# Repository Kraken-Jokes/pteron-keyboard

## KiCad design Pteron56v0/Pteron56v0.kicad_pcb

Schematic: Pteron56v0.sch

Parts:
C1, C4: 22p; 22pf_0603
C2, C3, C5: .1u; .1uf_0805
C6: 1u; .1uf_0805
C7: 10u; .1uf_0805
D1, D2, D3, D4, D5, D6, D7, D8, D9, D10, D11, D12, D13, D14, D15, D16, D17, D18, D19, D20, D21, D22, D23, D24, D25, D26, D27, D28, D29, D30, D31, D32, D33, D34, D35, D36, D37, D38, D39, D40, D41, D42, D43, D44, D45, D46, D47, D48, D49, D50, D51, D52, D53, D54, D55, D56: 1N4148; D_DO-35_SOD27_P7.62mm_Horizontal
D57, D58, D59, D60, D61, D62, D63, D64, D65, D66, D67, D68, D69, D70, D71, D72, D73, D74, D75, D76, D77, D78, D79, D80, D81, D82, D83, D84, D85, D86, D87, D88, D89, D90, D91, D92, D93, D94, D95, D96, D97, D98, D99, D100, D101, D102, D103, D104, D105, D106, D107, D108, D109, D110, D111, D112: LED; LED_0402_1005Metric
F1: 500mA; Fuse_0402_1005Metric
J1: USB_C_Receptacle_USB2.0; USB_C_Receptacle_XKB_U262-16XN-4BVC11
Q1: 2N2219; TO-39-3
R1, R2: 5.1k; R_0603_1608Metric
R3, R6: 10k; 10K_Resistor
R4, R5: 22; R_0805
R7: 10k; R_0805_2012Metric
R8, R9, R10, R11, R12, R13, R14, R15, R16, R17, R18, R19, R20, R21, R22, R23, R24, R25, R26, R27, R28, R29, R30, R31, R32, R33, R34, R35, R36, R37, R38, R39, R40, R41, R42, R43, R44, R45, R46, R47, R48, R49, R50, R51, R52, R53, R54, R55, R56, R57, R58, R59, R60, R61, R62, R63: 1k; R_0805_2012Metric
SW1, SW2, SW3, SW4, SW5, SW6, SW7, SW8, SW9, SW10, SW11, SW12, SW13, SW14, SW15, SW16, SW17, SW18, SW19, SW20, SW21, SW22, SW23, SW24, SW25, SW26, SW27, SW28, SW29, SW30, SW31, SW32, SW33, SW34, SW35, SW36, SW37, SW38, SW39, SW40, SW41, SW42, SW43, SW44, SW45, SW46, SW47, SW48, SW49, SW50, SW51, SW52, SW53, SW54, SW55, SW56: SW_PUSH; Mx_Alps_100
SW57: SW_PUSH; SW_SPST_TL3342
U1: USBLC6-2SC6; SOT-23-6
U2: ATmega32U4-AU; TQFP-44_10x10mm_P0.8mm
X1: XTAL_GND; crystal_FA238-TSX3225

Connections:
Col0: D1.1 (K), D2.1 (K), D3.1 (K), D4.1 (K), D5.1 (K), U2.32
Col1: D6.1 (K), D7.1 (K), D8.1 (K), D9.1 (K), D10.1 (K), U2.31
Col2: D11.1 (K), D12.1 (K), D13.1 (K), D14.1 (K), D15.1 (K), U2.38
Col3: D16.1 (K), D17.1 (K), D18.1 (K), D19.1 (K), D20.1 (K), U2.39
Col4: D21.1 (K), D22.1 (K), D23.1 (K), D24.1 (K), U2.40
Col5: D25.1 (K), D26.1 (K), D27.1 (K), D28.1 (K), U2.41
Col6: D29.1 (K), D30.1 (K), D31.1 (K), D32.1 (K), U2.11
Col7: D33.1 (K), D34.1 (K), D35.1 (K), D36.1 (K), U2.25
Col8: D37.1 (K), D38.1 (K), D39.1 (K), D40.1 (K), D41.1 (K), U2.26
Col9: D42.1 (K), D43.1 (K), D44.1 (K), D45.1 (K), D46.1 (K), U2.27
Col10: D47.1 (K), D48.1 (K), D49.1 (K), D50.1 (K), D51.1 (K), U2.30
Col11: D52.1 (K), D53.1 (K), D54.1 (K), D55.1 (K), D56.1 (K), U2.28
unnamed: C1.1, U2.17, X1.1
unnamed: C4.1, U2.16, X1.2
unnamed: C6.1, U2.6
unnamed: D1.2 (A), SW1.2
unnamed: D2.2 (A), SW2.2
unnamed: D3.2 (A), SW3.2
unnamed: D4.2 (A), SW4.2
unnamed: D5.2 (A), SW5.2
unnamed: D6.2 (A), SW6.2
unnamed: D7.2 (A), SW7.2
unnamed: D8.2 (A), SW8.2
unnamed: D9.2 (A), SW9.2
unnamed: D10.2 (A), SW10.2
unnamed: D11.2 (A), SW11.2
unnamed: D12.2 (A), SW12.2
unnamed: D13.2 (A), SW13.2
unnamed: D14.2 (A), SW14.2
unnamed: D15.2 (A), SW15.2
unnamed: D16.2 (A), SW16.2
unnamed: D17.2 (A), SW17.2
unnamed: D18.2 (A), SW18.2
unnamed: D19.2 (A), SW19.2
unnamed: D20.2 (A), SW20.2
unnamed: D21.2 (A), SW21.2
unnamed: D22.2 (A), SW22.2
unnamed: D23.2 (A), SW23.2
unnamed: D24.2 (A), SW24.2
unnamed: D25.2 (A), SW25.2
unnamed: D26.2 (A), SW26.2
unnamed: D27.2 (A), SW27.2
unnamed: D28.2 (A), SW28.2
unnamed: D29.2 (A), SW29.2
unnamed: D30.2 (A), SW30.2
unnamed: D31.2 (A), SW31.2
unnamed: D32.2 (A), SW32.2
unnamed: D33.2 (A), SW33.2
unnamed: D34.2 (A), SW34.2
unnamed: D35.2 (A), SW35.2
unnamed: D36.2 (A), SW36.2
unnamed: D37.2 (A), SW37.2
unnamed: D38.2 (A), SW38.2
unnamed: D39.2 (A), SW39.2
unnamed: D40.2 (A), SW40.2
unnamed: D41.2 (A), SW41.2
unnamed: D42.2 (A), SW42.2
unnamed: D43.2 (A), SW43.2
unnamed: D44.2 (A), SW44.2
unnamed: D45.2 (A), SW45.2
unnamed: D46.2 (A), SW46.2
unnamed: D47.2 (A), SW47.2
unnamed: D48.2 (A), SW48.2
unnamed: D49.2 (A), SW49.2
unnamed: D50.2 (A), SW50.2
unnamed: D51.2 (A), SW51.2
unnamed: D52.2 (A), SW52.2
unnamed: D53.2 (A), SW53.2
unnamed: D54.2 (A), SW54.2
unnamed: D55.2 (A), SW55.2
unnamed: D56.2 (A), SW56.2
unnamed: D57.2 (A), R8.1
unnamed: D58.2 (A), R9.1
unnamed: D59.2 (A), R10.1
unnamed: D60.2 (A), R11.1
unnamed: D61.2 (A), R12.1
unnamed: D62.2 (A), R13.1
unnamed: D63.2 (A), R14.1
unnamed: D64.2 (A), R15.1
unnamed: D65.2 (A), R16.1
unnamed: D66.2 (A), R17.1
unnamed: D67.2 (A), R18.1
unnamed: D68.2 (A), R19.1
unnamed: D69.2 (A), R20.1
unnamed: D70.2 (A), R21.1
unnamed: D71.2 (A), R22.1
unnamed: D72.2 (A), R23.1
unnamed: D73.2 (A), R24.1
unnamed: D74.2 (A), R25.1
unnamed: D75.2 (A), R26.1
unnamed: D76.2 (A), R27.1
unnamed: D77.2 (A), R28.1
unnamed: D78.2 (A), R29.1
unnamed: D79.2 (A), R30.1
unnamed: D80.2 (A), R31.1
unnamed: D81.2 (A), R32.1
unnamed: D82.2 (A), R33.1
unnamed: D83.2 (A), R34.1
unnamed: D84.2 (A), R35.1
unnamed: D85.2 (A), R36.1
unnamed: D86.2 (A), R37.1
unnamed: D87.2 (A), R38.1
unnamed: D88.2 (A), R39.1
unnamed: D89.2 (A), R40.1
unnamed: D90.2 (A), R41.1
unnamed: D91.2 (A), R42.1
unnamed: D92.2 (A), R43.1
unnamed: D93.2 (A), R44.1
unnamed: D94.2 (A), R45.1
unnamed: D95.2 (A), R46.1
unnamed: D96.2 (A), R47.1
unnamed: D98.2 (A), R49.1
unnamed: D99.2 (A), R50.1
unnamed: D57.1 (K), D58.1 (K), D59.1 (K), D60.1 (K), D61.1 (K), D62.1 (K), D63.1 (K), D64.1 (K), D65.1 (K), D66.1 (K), D67.1 (K), D68.1 (K), D69.1 (K), D70.1 (K), D71.1 (K), D72.1 (K), D73.1 (K), D74.1 (K), D75.1 (K), D76.1 (K), D77.1 (K), D78.1 (K), D79.1 (K), D80.1 (K), D81.1 (K), D82.1 (K), D83.1 (K), D84.1 (K), D85.1 (K), D86.1 (K), D87.1 (K), D88.1 (K), D89.1 (K), D90.1 (K), D91.1 (K), D92.1 (K), D93.1 (K), D94.1 (K), D95.1 (K), D96.1 (K), D97.1 (K), D98.1 (K), D99.1 (K), D100.1 (K), D101.1 (K), D102.1 (K), D103.1 (K), D104.1 (K), D105.1 (K), D106.1 (K), D107.1 (K), D108.1 (K), D109.1 (K), D110.1 (K), D111.1 (K), D112.1 (K), Q1.1 (E)
unnamed: D100.2 (A), R51.1
unnamed: D101.2 (A), R52.1
unnamed: D102.2 (A), R53.1
unnamed: D103.2 (A), R54.1
unnamed: D104.2 (A), R55.1
unnamed: D105.2 (A), R56.1
unnamed: D106.2 (A), R57.1
unnamed: D107.2 (A), R58.1
unnamed: D108.2 (A), R59.1
unnamed: D109.2 (A), R60.1
unnamed: D110.2 (A), R61.1
unnamed: D111.2 (A), R62.1
unnamed: D112.2 (A), R63.1
unnamed: F1.2, J1.A4, J1.A9, J1.B4, J1.B9
unnamed: J1.A5, R1.2
unnamed: J1.A6, J1.B6, U1.6
unnamed: J1.A7, J1.B7, U1.4
unnamed: J1.B5, R2.2
unnamed: Q1.2 (B), R7.1, U2.29
unnamed: R3.1, SW57.2, U2.13
unnamed: R4.1, U2.4
unnamed: R4.2, U1.1
unnamed: R5.1, U2.3
unnamed: R5.2, U1.3
unnamed: R6.2, U2.33
Row0: SW1.1, SW6.1, SW11.1, SW16.1, SW21.1, SW25.1, SW29.1, SW33.1, SW37.1, SW42.1, SW47.1, SW52.1, U2.10
Row1: SW2.1, SW7.1, SW12.1, SW17.1, SW22.1, SW26.1, SW30.1, SW34.1, SW38.1, SW43.1, SW48.1, SW53.1, U2.9
Row2: SW3.1, SW8.1, SW13.1, SW18.1, SW23.1, SW27.1, SW31.1, SW35.1, SW39.1, SW44.1, SW49.1, SW54.1, U2.20
Row3: SW4.1, SW9.1, SW14.1, SW19.1, SW24.1, SW28.1, SW32.1, SW36.1, SW40.1, SW45.1, SW50.1, SW55.1, U2.21
Row4: SW5.1, SW10.1, SW15.1, SW20.1, SW41.1, SW46.1, SW51.1, SW56.1, U2.37
VCC: R8.2, R9.2, R10.2, R11.2, R12.2, R13.2, R14.2, R15.2, R16.2, R17.2, R18.2, R19.2, R20.2, R21.2, R22.2, R23.2, R24.2, R25.2, R26.2, R27.2, R28.2, R29.2, R30.2, R31.2, R32.2, R33.2, R34.2, R35.2, R36.2, R37.2, R38.2, R39.2, R40.2, R41.2, R42.2, R43.2, R44.2, R45.2, R46.2, R47.2, R48.2, R49.2, R50.2, R51.2, R52.2, R53.2, R54.2, R55.2, R56.2, R57.2, R58.2, R59.2, R60.2, R61.2, R62.2, R63.2

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
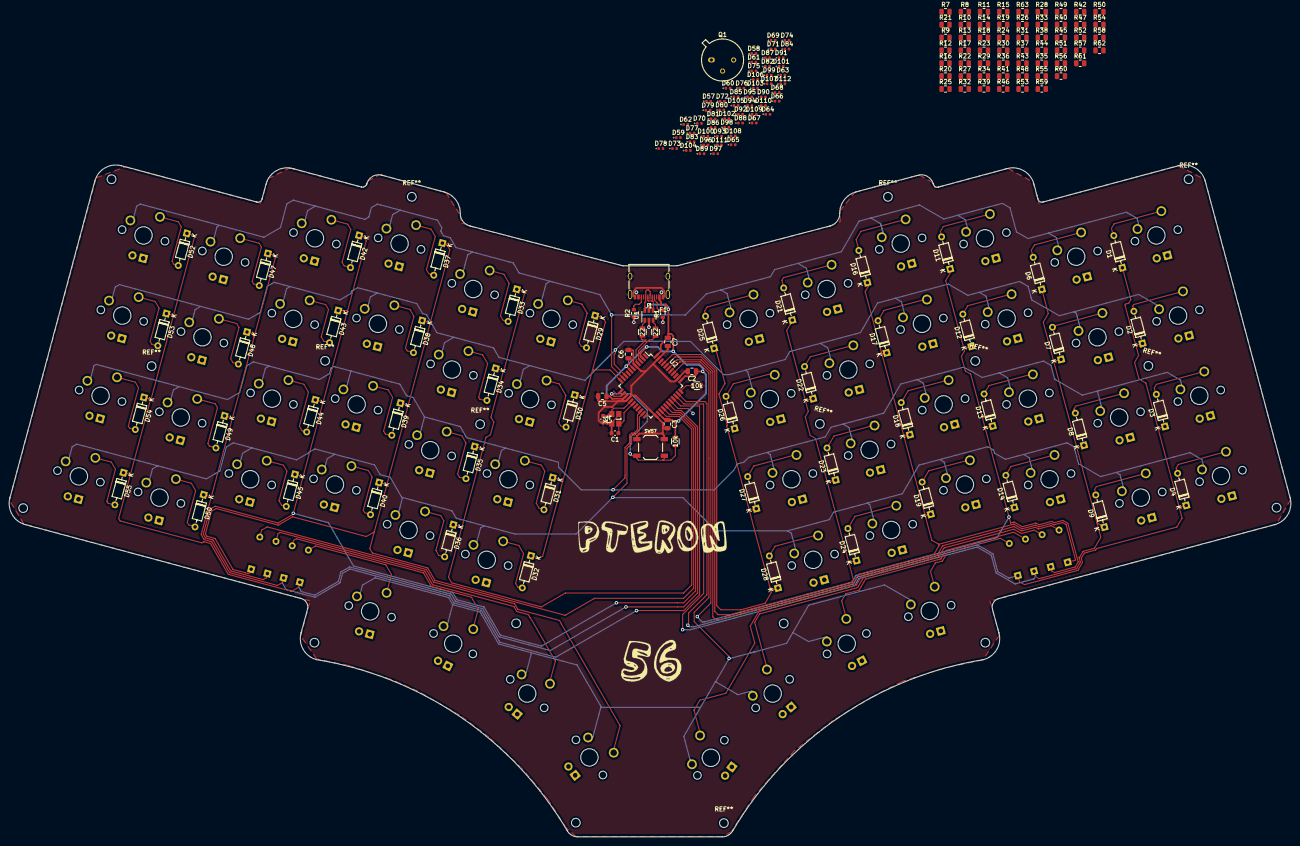
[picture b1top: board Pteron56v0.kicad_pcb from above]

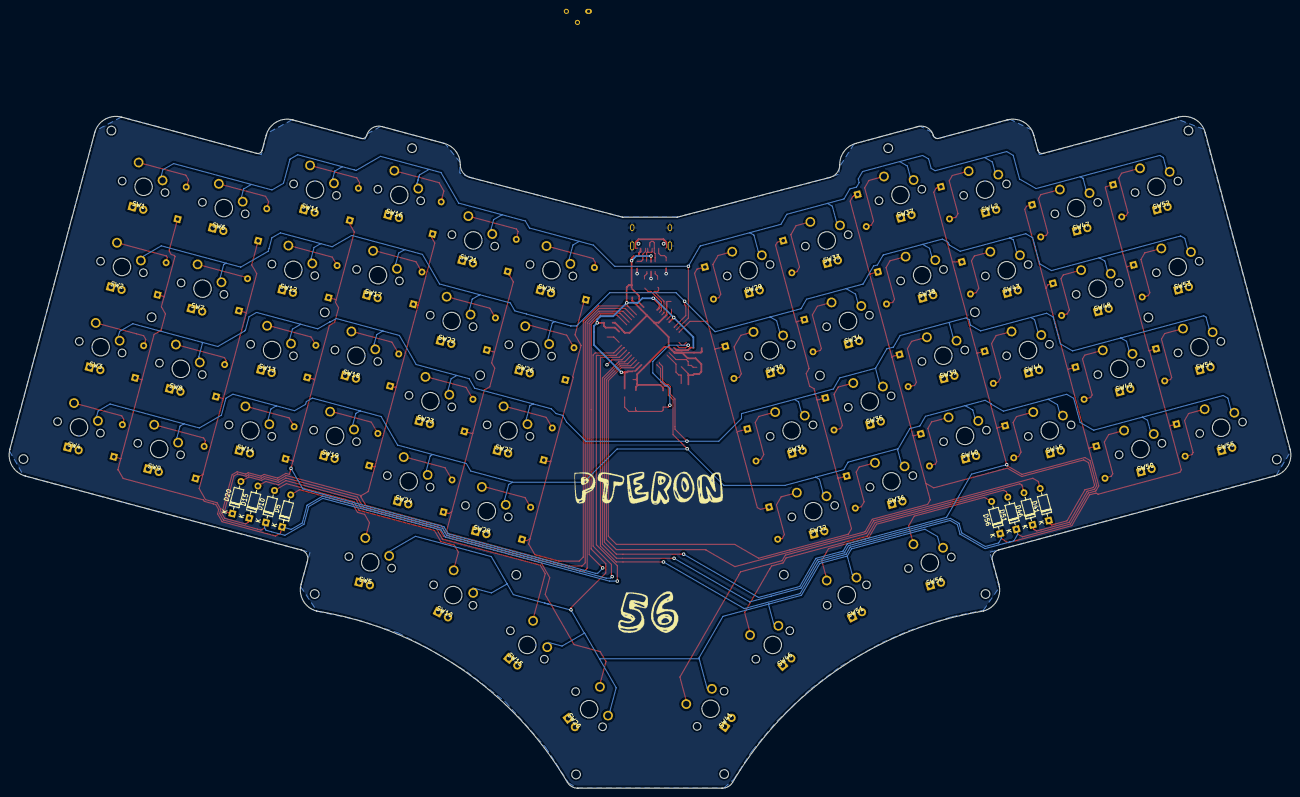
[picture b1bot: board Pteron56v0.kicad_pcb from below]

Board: 2 copper layers, 293.7 x 154.0 mm, 245 parts (8 on the bottom side), 147 nets.

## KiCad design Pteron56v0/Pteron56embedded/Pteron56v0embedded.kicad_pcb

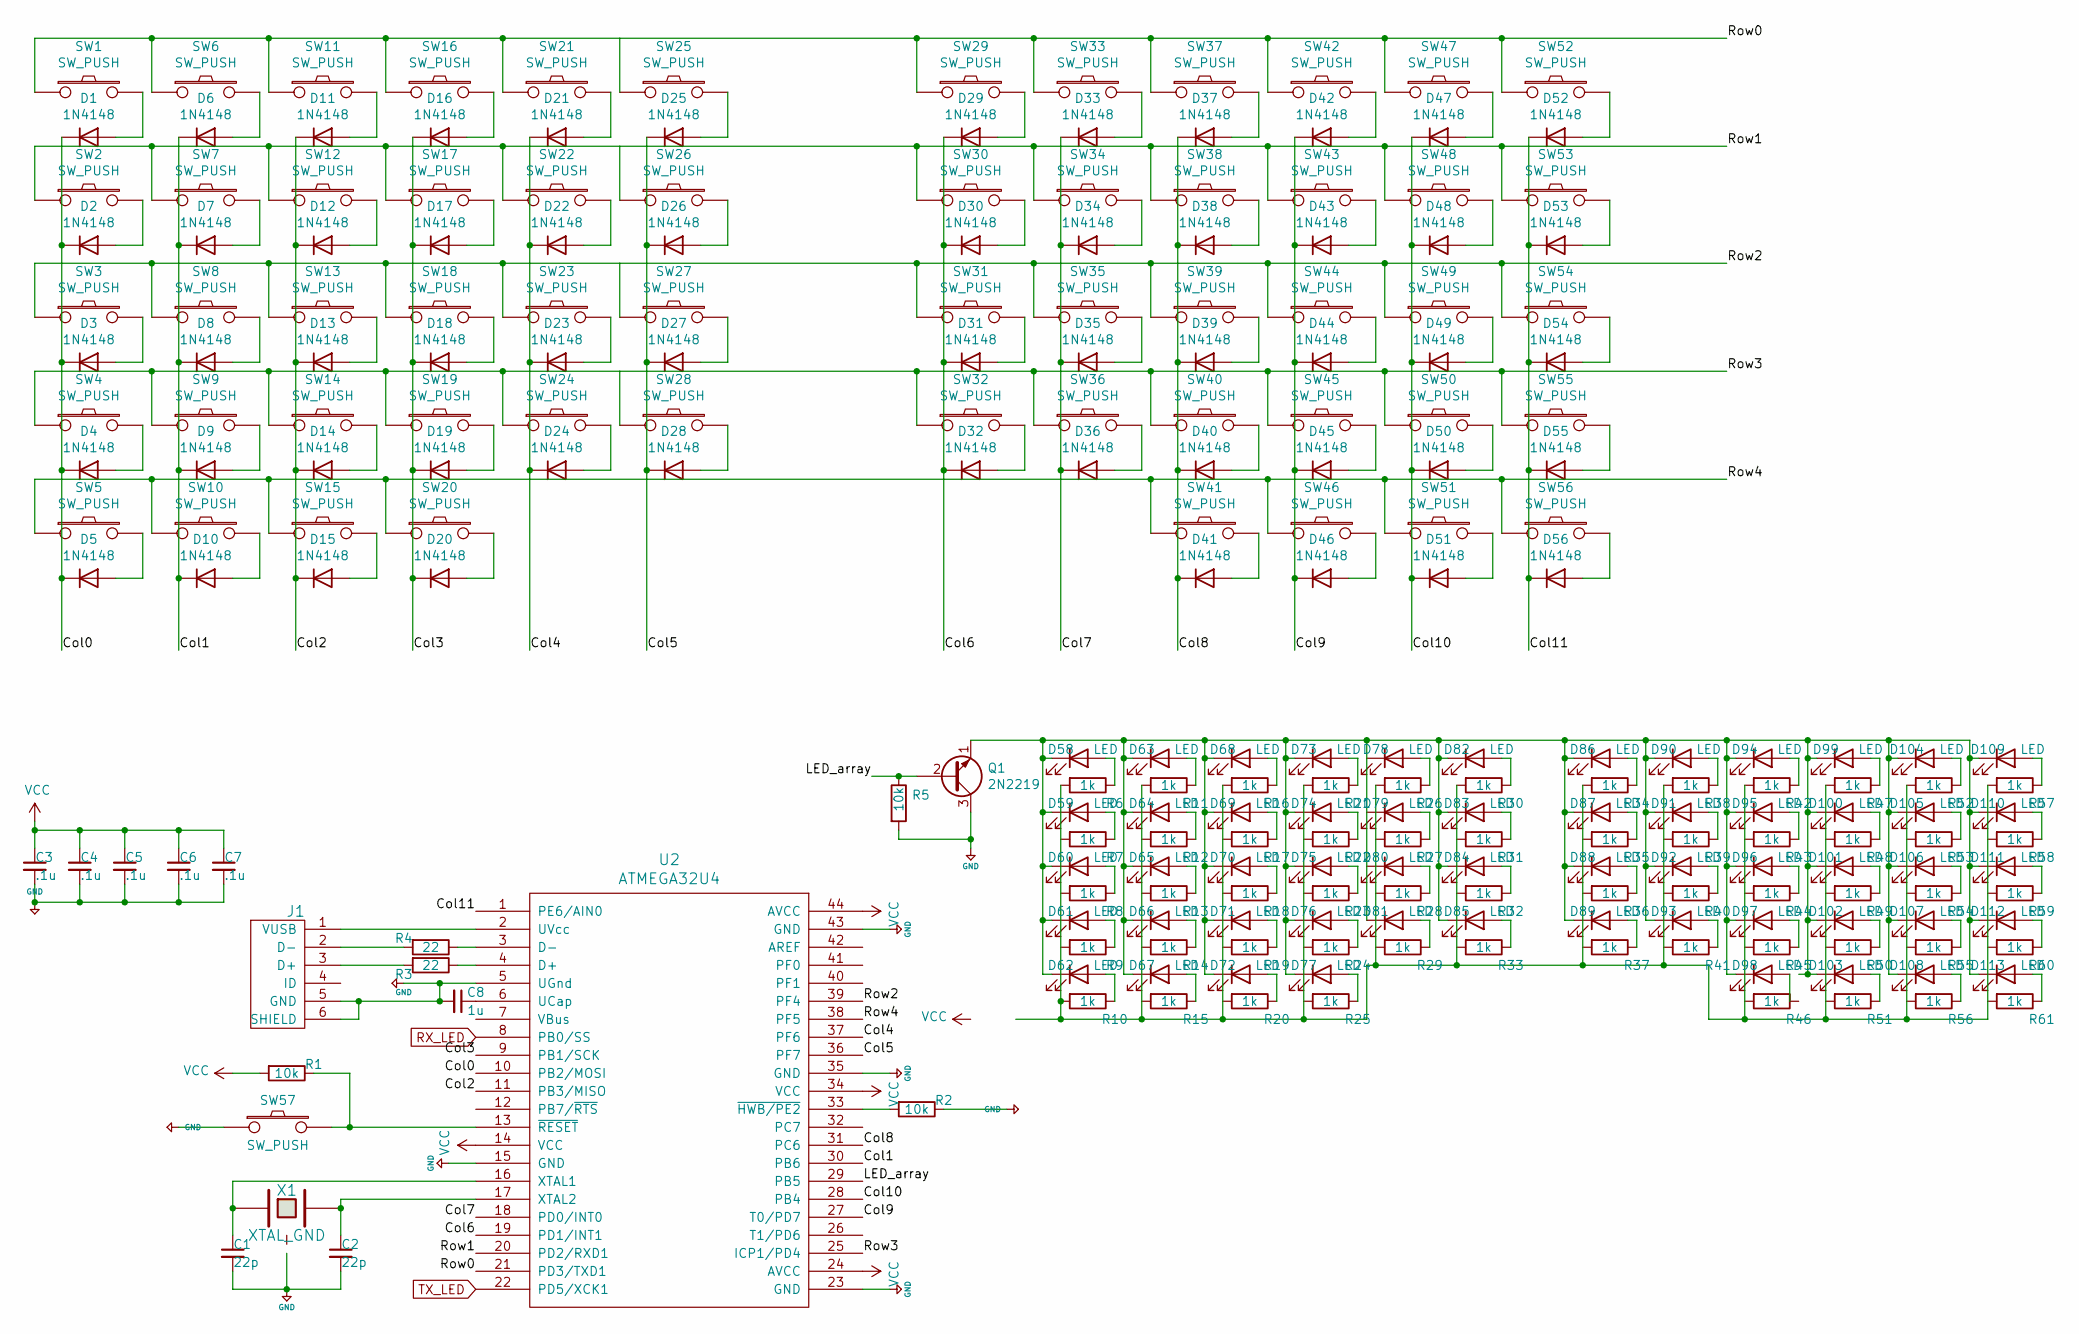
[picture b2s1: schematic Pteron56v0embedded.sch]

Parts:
C1, C2: 22p; 22pf_0603
C3, C4, C5, C6, C7: .1u; .1uf_0805
C8: 1u; .1uf_0805
D1, D2, D3, D4, D5, D6, D7, D8, D9, D10, D11, D12, D13, D14, D15, D16, D17, D18, D19, D20, D21, D22, D23, D24, D25, D26, D27, D28, D29, D30, D31, D32, D33, D34, D35, D36, D37, D38, D39, D40, D41, D42, D43, D44, D45, D46, D47, D48, D49, D50, D51, D52, D53, D54, D55, D56: 1N4148; D_DO-35_SOD27_P7.62mm_Horizontal
D58, D59, D60, D61, D62, D63, D64, D65, D66, D67, D68, D69, D70, D71, D72, D73, D74, D75, D76, D77, D78, D79, D80, D81, D82, D83, D84, D85, D86, D87, D88, D89, D90, D91, D92, D93, D94, D95, D96, D97, D98, D99, D100, D101, D102, D103, D104, D105, D106, D107, D108, D109, D110, D111, D112, D113: LED; LED_D1.8mm_W3.3mm_H2.4mm
J1: USB_mini_micro_B; USB-Mini-B_2leg
Q1: 2N2219; TO-39-3
R1, R2: 10k; 10K_Resistor
R3, R4: 22; 1K_Resistor
R5: 10k; 1K_Resistor
R6, R7, R8, R9, R10, R11, R12, R13, R14, R15, R16, R17, R18, R19, R20, R21, R22, R23, R24, R25, R26, R27, R28, R29, R30, R31, R32, R33, R34, R35, R36, R37, R38, R39, R40, R41, R42, R43, R44, R45, R46, R47, R48, R49, R50, R51, R52, R53, R54, R55, R56, R57, R58, R59, R60, R61: 1k; 1K_Resistor
SW1, SW2, SW3, SW4, SW5, SW6, SW7, SW8, SW9, SW10, SW11, SW12, SW13, SW14, SW15, SW16, SW17, SW18, SW19, SW20, SW21, SW22, SW23, SW24, SW25, SW26, SW27, SW28, SW29, SW30, SW31, SW32, SW33, SW34, SW35, SW36, SW37, SW38, SW39, SW40, SW41, SW42, SW43, SW44, SW45, SW46, SW47, SW48, SW49, SW50, SW51, SW52, SW53, SW54, SW55, SW56: SW_PUSH; Mx_Alps_100
SW57: SW_PUSH; SW_SPST_TL3342
U2: ATMEGA32U4; ATMEGA32U4-AU
X1: XTAL_GND; crystal_FA238-TSX3225

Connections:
+5V: C1.2, C2.2, C3.2, C4.2, C5.2, C6.2, C7.2, C8.2, J1.5 (GND), J1.6 (SHIELD), Q1.3 (C), R2.1, R5.2, SW57.1, U2.5 (UGnd), U2.15 (GND), U2.23 (GND), U2.35 (GND), U2.43 (GND)
/Col0: D1.1 (K), D2.1 (K), D3.1 (K), D4.1 (K), D5.1 (K), U2.10 (PB2/MOSI)
/Col1: D6.1 (K), D7.1 (K), D8.1 (K), D9.1 (K), D10.1 (K), U2.30 (PB6)
/Col2: D11.1 (K), D12.1 (K), D13.1 (K), D14.1 (K), D15.1 (K), U2.11 (PB3/MISO)
/Col3: D16.1 (K), D17.1 (K), D18.1 (K), D19.1 (K), D20.1 (K), U2.9 (PB1/SCK)
/Col4: D21.1 (K), D22.1 (K), D23.1 (K), D24.1 (K), U2.37 (PF6)
/Col5: D25.1 (K), D26.1 (K), D27.1 (K), D28.1 (K), U2.36 (PF7)
/Col6: D29.1 (K), D30.1 (K), D31.1 (K), D32.1 (K), U2.19 (PD1/INT1)
/Col7: D33.1 (K), D34.1 (K), D35.1 (K), D36.1 (K), U2.18 (PD0/INT0)
/Col8: D37.1 (K), D38.1 (K), D39.1 (K), D40.1 (K), D41.1 (K), U2.31 (PC6)
/Col9: D42.1 (K), D43.1 (K), D44.1 (K), D45.1 (K), D46.1 (K), U2.27 (T0/PD7)
/Col10: D47.1 (K), D48.1 (K), D49.1 (K), D50.1 (K), D51.1 (K), U2.28 (PB4)
/Col11: D52.1 (K), D53.1 (K), D54.1 (K), D55.1 (K), D56.1 (K), U2.1 (PE6/AIN0)
/LED_array: Q1.2 (B), R5.1, U2.29 (PB5)
/Row0: SW1.1, SW6.1, SW11.1, SW16.1, SW21.1, SW25.1, SW29.1, SW33.1, SW37.1, SW42.1, SW47.1, SW52.1, U2.21 (PD3/TXD1)
/Row1: SW2.1, SW7.1, SW12.1, SW17.1, SW22.1, SW26.1, SW30.1, SW34.1, SW38.1, SW43.1, SW48.1, SW53.1, U2.20 (PD2/RXD1)
/Row2: SW3.1, SW8.1, SW13.1, SW18.1, SW23.1, SW27.1, SW31.1, SW35.1, SW39.1, SW44.1, SW49.1, SW54.1, U2.39 (PF4)
/Row3: SW4.1, SW9.1, SW14.1, SW19.1, SW24.1, SW28.1, SW32.1, SW36.1, SW40.1, SW45.1, SW50.1, SW55.1, U2.25 (ICP1/PD4)
/Row4: SW5.1, SW10.1, SW15.1, SW20.1, SW41.1, SW46.1, SW51.1, SW56.1, U2.38 (PF5)
unnamed: C1.1, U2.16 (XTAL1), X1.1
unnamed: C2.1, U2.17 (XTAL2), X1.2
unnamed: C8.1, U2.6 (UCap)
unnamed: D1.2 (A), SW1.2
unnamed: D2.2 (A), SW2.2
unnamed: D3.2 (A), SW3.2
unnamed: D4.2 (A), SW4.2
unnamed: D5.2 (A), SW5.2
unnamed: D6.2 (A), SW6.2
unnamed: D7.2 (A), SW7.2
unnamed: D8.2 (A), SW8.2
unnamed: D9.2 (A), SW9.2
unnamed: D10.2 (A), SW10.2
unnamed: D11.2 (A), SW11.2
unnamed: D12.2 (A), SW12.2
unnamed: D13.2 (A), SW13.2
unnamed: D14.2 (A), SW14.2
unnamed: D15.2 (A), SW15.2
unnamed: D16.2 (A), SW16.2
unnamed: D17.2 (A), SW17.2
unnamed: D18.2 (A), SW18.2
unnamed: D19.2 (A), SW19.2
unnamed: D20.2 (A), SW20.2
unnamed: D21.2 (A), SW21.2
unnamed: D22.2 (A), SW22.2
unnamed: D23.2 (A), SW23.2
unnamed: D24.2 (A), SW24.2
unnamed: D25.2 (A), SW25.2
unnamed: D26.2 (A), SW26.2
unnamed: D27.2 (A), SW27.2
unnamed: D28.2 (A), SW28.2
unnamed: D29.2 (A), SW29.2
unnamed: D30.2 (A), SW30.2
unnamed: D31.2 (A), SW31.2
unnamed: D32.2 (A), SW32.2
unnamed: D33.2 (A), SW33.2
unnamed: D34.2 (A), SW34.2
unnamed: D35.2 (A), SW35.2
unnamed: D36.2 (A), SW36.2
unnamed: D37.2 (A), SW37.2
unnamed: D38.2 (A), SW38.2
unnamed: D39.2 (A), SW39.2
unnamed: D40.2 (A), SW40.2
unnamed: D41.2 (A), SW41.2
unnamed: D42.2 (A), SW42.2
unnamed: D43.2 (A), SW43.2
unnamed: D44.2 (A), SW44.2
unnamed: D45.2 (A), SW45.2
unnamed: D46.2 (A), SW46.2
unnamed: D47.2 (A), SW47.2
unnamed: D48.2 (A), SW48.2
unnamed: D49.2 (A), SW49.2
unnamed: D50.2 (A), SW50.2
unnamed: D51.2 (A), SW51.2
unnamed: D52.2 (A), SW52.2
unnamed: D53.2 (A), SW53.2
unnamed: D54.2 (A), SW54.2
unnamed: D55.2 (A), SW55.2
unnamed: D56.2 (A), SW56.2
unnamed: D58.2 (A), R6.1
unnamed: D59.2 (A), R7.1
unnamed: D60.2 (A), R8.1
unnamed: D61.2 (A), R9.1
unnamed: D62.2 (A), R10.1
unnamed: D63.2 (A), R11.1
unnamed: D64.2 (A), R12.1
unnamed: D65.2 (A), R13.1
unnamed: D66.2 (A), R14.1
unnamed: D67.2 (A), R15.1
unnamed: D68.2 (A), R16.1
unnamed: D69.2 (A), R17.1
unnamed: D70.2 (A), R18.1
unnamed: D71.2 (A), R19.1
unnamed: D72.2 (A), R20.1
unnamed: D73.2 (A), R21.1
unnamed: D74.2 (A), R22.1
unnamed: D75.2 (A), R23.1
unnamed: D76.2 (A), R24.1
unnamed: D77.2 (A), R25.1
unnamed: D78.2 (A), R26.1
unnamed: D79.2 (A), R27.1
unnamed: D80.2 (A), R28.1
unnamed: D81.2 (A), R29.1
unnamed: D82.2 (A), R30.1
unnamed: D83.2 (A), R31.1
unnamed: D84.2 (A), R32.1
unnamed: D85.2 (A), R33.1
unnamed: D86.2 (A), R34.1
unnamed: D87.2 (A), R35.1
unnamed: D88.2 (A), R36.1
unnamed: D89.2 (A), R37.1
unnamed: D90.2 (A), R38.1
unnamed: D91.2 (A), R39.1
unnamed: D92.2 (A), R40.1
unnamed: D93.2 (A), R41.1
unnamed: D94.2 (A), R42.1
unnamed: D95.2 (A), R43.1
unnamed: D96.2 (A), R44.1
unnamed: D97.2 (A), R45.1
unnamed: D99.2 (A), R47.1
unnamed: D58.1 (K), D59.1 (K), D60.1 (K), D61.1 (K), D62.1 (K), D63.1 (K), D64.1 (K), D65.1 (K), D66.1 (K), D67.1 (K), D68.1 (K), D69.1 (K), D70.1 (K), D71.1 (K), D72.1 (K), D73.1 (K), D74.1 (K), D75.1 (K), D76.1 (K), D77.1 (K), D81.1 (K), D82.1 (K), D83.1 (K), D84.1 (K), D85.1 (K), D86.1 (K), D87.1 (K), D88.1 (K), D89.1 (K), D90.1 (K), D91.1 (K), D92.1 (K), D93.1 (K), D94.1 (K), D95.1 (K), D96.1 (K), D97.1 (K), D98.1 (K), D99.1 (K), D100.1 (K), D101.1 (K), D102.1 (K), D103.1 (K), D104.1 (K), D105.1 (K), D106.1 (K), D107.1 (K), D108.1 (K), D109.1 (K), D110.1 (K), D111.1 (K), D112.1 (K), D113.1 (K), Q1.1 (E)
unnamed: D100.2 (A), R48.1
unnamed: D101.2 (A), R49.1
unnamed: D102.2 (A), R50.1
unnamed: D103.2 (A), R51.1
unnamed: D104.2 (A), R52.1
unnamed: D105.2 (A), R53.1
unnamed: D106.2 (A), R54.1
unnamed: D107.2 (A), R55.1
unnamed: D108.2 (A), R56.1
unnamed: D109.2 (A), R57.1
unnamed: D110.2 (A), R58.1
unnamed: D111.2 (A), R59.1
unnamed: D112.2 (A), R60.1
unnamed: D113.2 (A), R61.1
unnamed: J1.1 (VUSB), U2.2 (UVcc)
unnamed: J1.2 (D-), R4.2
unnamed: J1.3 (D+), R3.2
unnamed: R1.1, SW57.2, U2.13 (~RESET)
unnamed: R2.2, U2.33 (~HWB/PE2)
unnamed: R3.1, U2.4 (D+)
unnamed: R4.1, U2.3 (D-)
unnamed: R6.2, R10.2, R11.2, R16.2, R21.2, R26.2, R30.2, R34.2, R38.2, R42.2, R47.2, R52.2, R57.2
RX_LED: U2.8 (PB0/SS)
TX_LED: U2.22 (PD5/XCK1)
VCC: C3.1, C4.1, C5.1, C6.1, C7.1, R1.2, U2.14 (VCC), U2.24 (AVCC), U2.34 (VCC), U2.44 (AVCC)

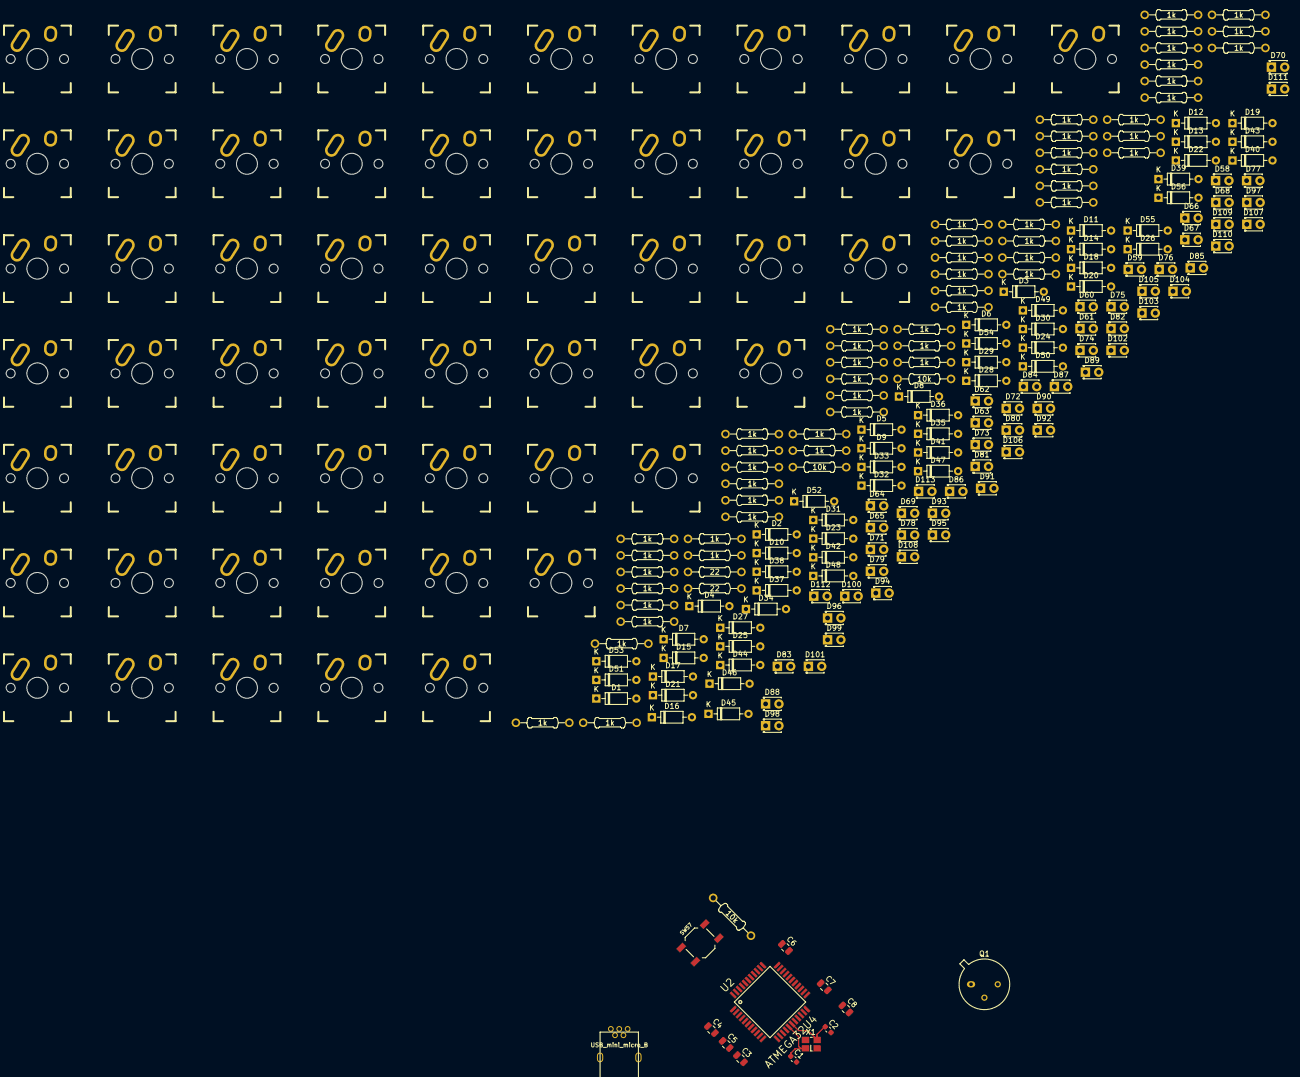
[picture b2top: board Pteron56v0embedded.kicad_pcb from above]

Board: 2 copper layers, 242 parts (0 on the bottom side), 143 nets.

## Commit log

2021-01-04 Delete Pteron56_logo.png
    Tangental to /main, so unincluded
2021-01-04 Delete Pteron56_logo.svg
    Tangental to /main, so unincluded
2021-03-14 PCB KiCAD files
    only has support for a pro micro and switches so far
2021-03-14 PCB renders
    Added to /pteron56v0 initially, wanted to add a section for them
2021-03-14 Delete Pteron56v0blue.png
    redundant
2021-03-14 Delete Pteron56v0.jpg
    redundant
2021-03-14 Delete Pteron56v0blue2.jpg
    redundant
2021-03-14 Delete Pteron56v0white.png
    redundant
2021-03-14 Delete Pteron56v0purple.png
    redundant
2021-03-14 Delete Pteron56v0.png
    redundant
2021-03-14 Delete _autosave-Pteron56v0.sch
    redundant
2021-03-15 Embedded 32u4
    Incomplete
2021-03-16 Add files via upload
    Updates, added usb C 32u4-au
2021-03-17 Add files via upload
    More edits, finished the MCU.
    TODO:
    THT LEDs
    WS2812b underglow
    Add EC11 encoder
2021-03-17 Add files via upload
    Forgot the updated NET
2021-03-17 Delete Pteron56v0/Pteron56embedded directory
    Redundant, I embedded the main board
2021-03-17 Add files via upload
    Forgot some more files
2021-03-21 Pro Micro compatible PCB
    More is in the works, but this is a great start!
